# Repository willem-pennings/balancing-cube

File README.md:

## Balancing cube

This repository contains all design, documentation, configuration and other files related to the balancing cube that I have designed and built.
* Mechanical parts are designed in [Fusion 360](https://www.autodesk.com/products/fusion-360/personal).
* Circuit boards are designed in [KiCad 7](https://www.kicad.org/download/windows/).
* Code has been written using [Arduino IDE](https://docs.arduino.cc/software/ide-v2/tutorials/getting-started/ide-v2-downloading-and-installing/).
* Motor drivers are commissioned and tuned using [Escon Studio](https://www.maxongroup.nl/maxon/view/content/ESCON-Detailsite?isoCode=nl).
* Motors and motor controllers are available from [Maxon](https://www.maxongroup.com/maxon/view/content/index).
* Circuit boards and custom mechanical parts can be ordered from [PCBWay](https://www.pcbway.com/rapid-prototyping/), for example.

A YouTube video demonstrating the balancing cube is available [here](https://youtu.be/zGclFqkZBsk).

### Want to build one? Read this!

This repository should contain everything you need to order and/or build parts for this cube. Take into account the following:

* I replaced four of the eight 16AWG wires in each cable assembly by 22AWG wires since only four wires carry large currents. The others carry +5V and hall sensor signals. This reduces weight and makes the cables easier to handle, as well as reducing strain on the mating connectors. The motor connection is rather fragile and might break if stressed too much.
* The ESP32 board does not go into flashing mode automatically. I fixed this by adding a 10 uF capacitor between the enable and reset pin, as described [here](https://randomnerdtutorials.com/solved-failed-to-connect-to-esp32-timed-out-waiting-for-packet-header/).
* In my blog post, I describe some errors in the design of the motherboard. These have been resolved in the files that are available in this repository.
* For your own safety, I highly recommend taking precautions to reduce the risk of trapping fingers between the spinning flywheels. One option is to attach very thin (spring steel) discs to each wheel, which may be (laser)cut from larger sheets that are readily available. I do not have designs available for such safety devices yet.

### More information

More information about this project and my other projects is available on my [website](https://willempennings.nl/balancing-cube/).

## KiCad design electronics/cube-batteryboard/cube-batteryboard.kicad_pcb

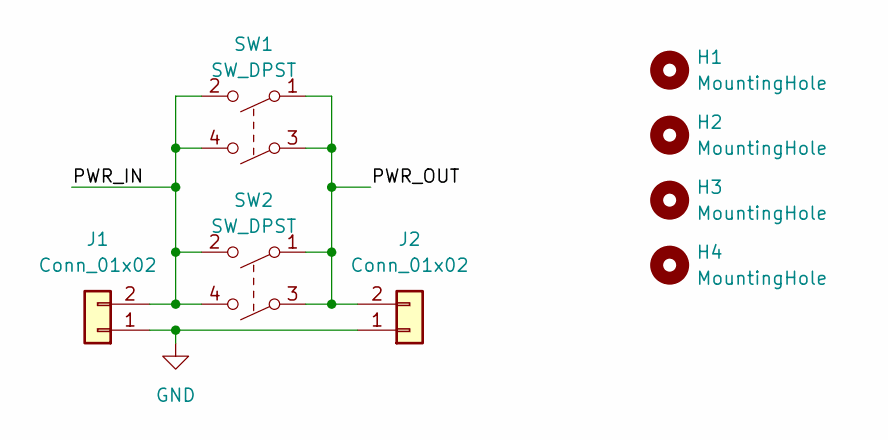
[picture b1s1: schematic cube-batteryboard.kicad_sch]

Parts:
H1, H2, H3, H4: MountingHole; MountingHole_3.2mm_M3_DIN965_Pad
J1: Conn_01x02; AMASS_XT60-M_1x02_P7.20mm_Vertical
J2: Conn_01x02; AMASS_XT60-F_1x02_P7.20mm_Vertical
SW1, SW2: SW_DPST; L201011MS02Q

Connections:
/PWR_IN: J1.2, SW1.2, SW1.4, SW2.2, SW2.4
/PWR_OUT: J2.2, SW1.1, SW1.3, SW2.1, SW2.3
GND: J1.1, J2.1

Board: 2 copper layers, 13 parts (9 on the bottom side), 3 nets, no tracks yet.

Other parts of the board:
kibuzzard-65634FCA: G***; kibuzzard-65634FCA
kibuzzard-656351C1: G***; kibuzzard-656351C1
kibuzzard-656351D2: G***; kibuzzard-656351D2
kibuzzard-656351E7: G***; kibuzzard-656351E7
kibuzzard-65635119: G***; kibuzzard-65635119

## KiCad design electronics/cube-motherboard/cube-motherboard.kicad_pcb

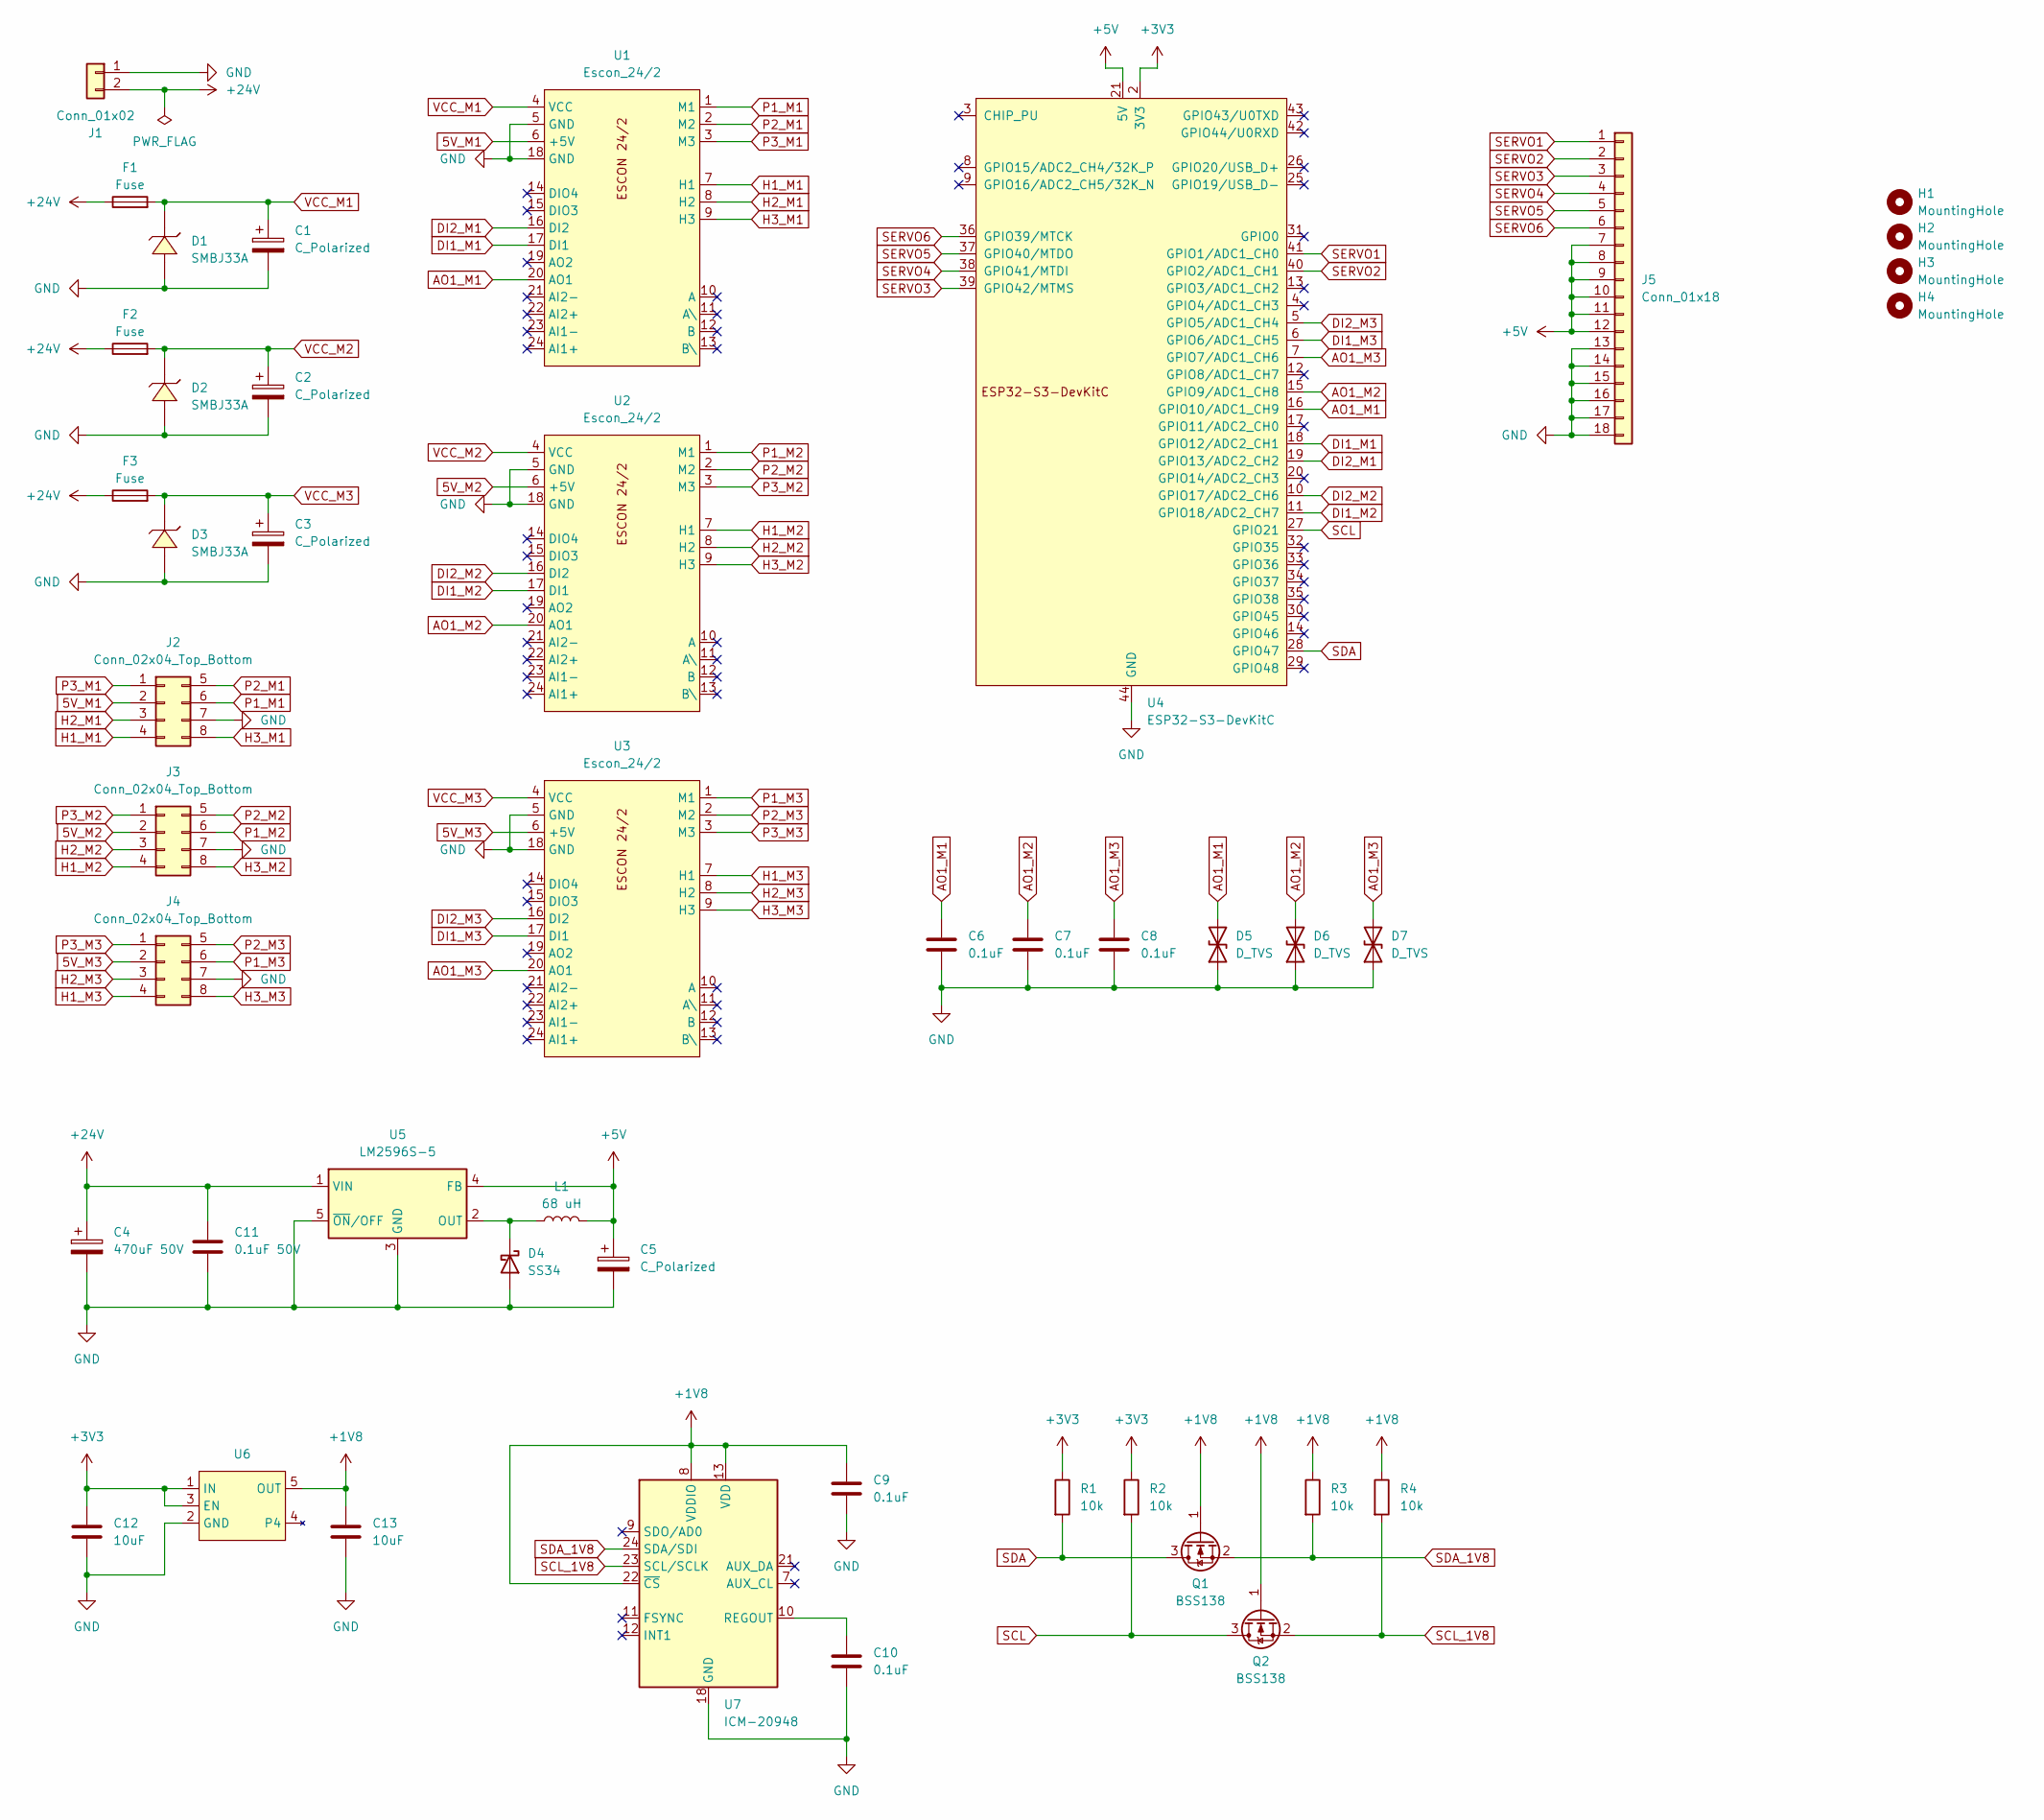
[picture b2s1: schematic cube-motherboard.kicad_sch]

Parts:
C1, C2, C3: C_Polarized; CP_Radial_D12.5mm_P5.00mm
C4: 470uF 50V; CP_Radial_D18.0mm_P7.50mm
C5: C_Polarized; CP_Radial_D10.0mm_P5.00mm
C6, C7, C8, C9, C10: 0.1uF; C_0603_1608Metric
C11: 0.1uF 50V; C_0603_1608Metric
C12, C13: 10uF; C_0603_1608Metric
D1, D2, D3: SMBJ33A; SMB_L4.4-W3.6-LS5.4-RD
D4: SS34; D_SOD-123F
D5, D6, D7: D_TVS; D_0402_1005Metric
F1, F2, F3: Fuse; Littelfuse 0157004.DR
H1, H2, H3, H4: MountingHole; MountingHole_3.2mm_M3_DIN965_Pad
J1: Conn_01x02; AMASS_XT60-F_1x02_P7.20mm_Vertical
J2, J3, J4: Conn_02x04_Top_Bottom; Molex_Mini-Fit_Jr_5566-08A_2x04_P4.20mm_Vertical
J5: Conn_01x18; PinHeader_03x06
L1: 68 uH; Bourns SRP1050WA-680M
Q1, Q2: BSS138; SOT-23
R1, R2, R3, R4: 10k; R_0603_1608Metric
U1, U2, U3: Escon_24/2; Escon_24
U4: ESP32-S3-DevKitC
U5: LM2596S-5; TO-263-5_TabPin3
U6: SOT-23-5
U7: ICM-20948; InvenSense_QFN-24_3x3mm_P0.4mm

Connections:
5V_M1: J2.2, U1.6 (+5V)
5V_M2: J3.2, U2.6 (+5V)
5V_M3: J4.2, U3.6 (+5V)
+1V8: C9.1, C13.1, Q1.1 (G), Q2.1 (G), R3.1, R4.1, U6.5 (OUT), U7.8 (VDDIO), U7.13 (VDD), U7.22 (~CS)
+3V3: C12.1, R1.1, R2.1, U4.1 (3V3), U4.2 (3V3), U6.1 (IN), U6.3 (EN)
+5V: C5.1, J5.7, J5.8, J5.9, J5.10, J5.11, J5.12, L1.2, U4.21 (5V), U5.4 (FB)
+24V: C4.1, C11.1, F1.1, F2.1, F3.1, J1.2, U5.1 (VIN)
AO1_M1: C6.1, D5.2 (A2), U1.20 (AO1), U4.16 (GPIO10/ADC1_CH9)
AO1_M2: C7.1, D6.2 (A2), U2.20 (AO1), U4.15 (GPIO9/ADC1_CH8)
AO1_M3: C8.1, D7.2 (A2), U3.20 (AO1), U4.7 (GPIO7/ADC1_CH6)
DI1_M1: U1.17 (DI1), U4.18 (GPIO12/ADC2_CH1)
DI1_M2: U2.17 (DI1), U4.11 (GPIO18/ADC2_CH7)
DI1_M3: U3.17 (DI1), U4.6 (GPIO6/ADC1_CH5)
DI2_M1: U1.16 (DI2), U4.19 (GPIO13/ADC2_CH2)
DI2_M2: U2.16 (DI2), U4.10 (GPIO17/ADC2_CH6)
DI2_M3: U3.16 (DI2), U4.5 (GPIO5/ADC1_CH4)
GND: C1.2, C2.2, C3.2, C4.2, C5.2, C6.2, C7.2, C8.2, C9.2, C10.2, C11.2, C12.2, C13.2, D1.2 (A), D2.2 (A), D3.2 (A), D4.2 (A), D5.1 (A1), D6.1 (A1), D7.1 (A1), J1.1, J2.7, J3.7, J4.7, J5.13, J5.14, J5.15, J5.16, J5.17, J5.18, U1.5 (GND), U1.18 (GND), U2.5 (GND), U2.18 (GND), U3.5 (GND), U3.18 (GND), U4.22 (GND), U4.23 (GND), U4.24 (GND), U4.44 (GND), U5.3 (GND), U5.5 (~ON/OFF), U6.2 (GND), U7.18 (GND), U7.20 (GND)
H1_M1: J2.4, U1.7 (H1)
H1_M2: J3.4, U2.7 (H1)
H1_M3: J4.4, U3.7 (H1)
H2_M1: J2.3, U1.8 (H2)
H2_M2: J3.3, U2.8 (H2)
H2_M3: J4.3, U3.8 (H2)
H3_M1: J2.8, U1.9 (H3)
H3_M2: J3.8, U2.9 (H3)
H3_M3: J4.8, U3.9 (H3)
unnamed: D4.1 (K), L1.1, U5.2 (OUT)
unnamed: C10.1, U7.10 (REGOUT)
P1_M1: J2.6, U1.1 (M1)
P1_M2: J3.6, U2.1 (M1)
P1_M3: J4.6, U3.1 (M1)
P2_M1: J2.5, U1.2 (M2)
P2_M2: J3.5, U2.2 (M2)
P2_M3: J4.5, U3.2 (M2)
P3_M1: J2.1, U1.3 (M3)
P3_M2: J3.1, U2.3 (M3)
P3_M3: J4.1, U3.3 (M3)
SCL: Q2.3 (D), R2.2, U4.27 (GPIO21)
SCL_1V8: Q2.2 (S), R4.2, U7.23 (SCL/SCLK)
SDA: Q1.3 (D), R1.2, U4.28 (GPIO47)
SDA_1V8: Q1.2 (S), R3.2, U7.24 (SDA/SDI)
SERVO1: J5.1, U4.41 (GPIO1/ADC1_CH0)
SERVO2: J5.2, U4.40 (GPIO2/ADC1_CH1)
SERVO3: J5.3, U4.39 (GPIO42/MTMS)
SERVO4: J5.4, U4.38 (GPIO41/MTDI)
SERVO5: J5.5, U4.37 (GPIO40/MTDO)
SERVO6: J5.6, U4.36 (GPIO39/MTCK)
VCC_M1: C1.1, D1.1 (C), F1.2, U1.4 (VCC)
VCC_M2: C2.1, D2.1 (C), F2.2, U2.4 (VCC)
VCC_M3: C3.1, D3.1 (C), F3.2, U3.4 (VCC)

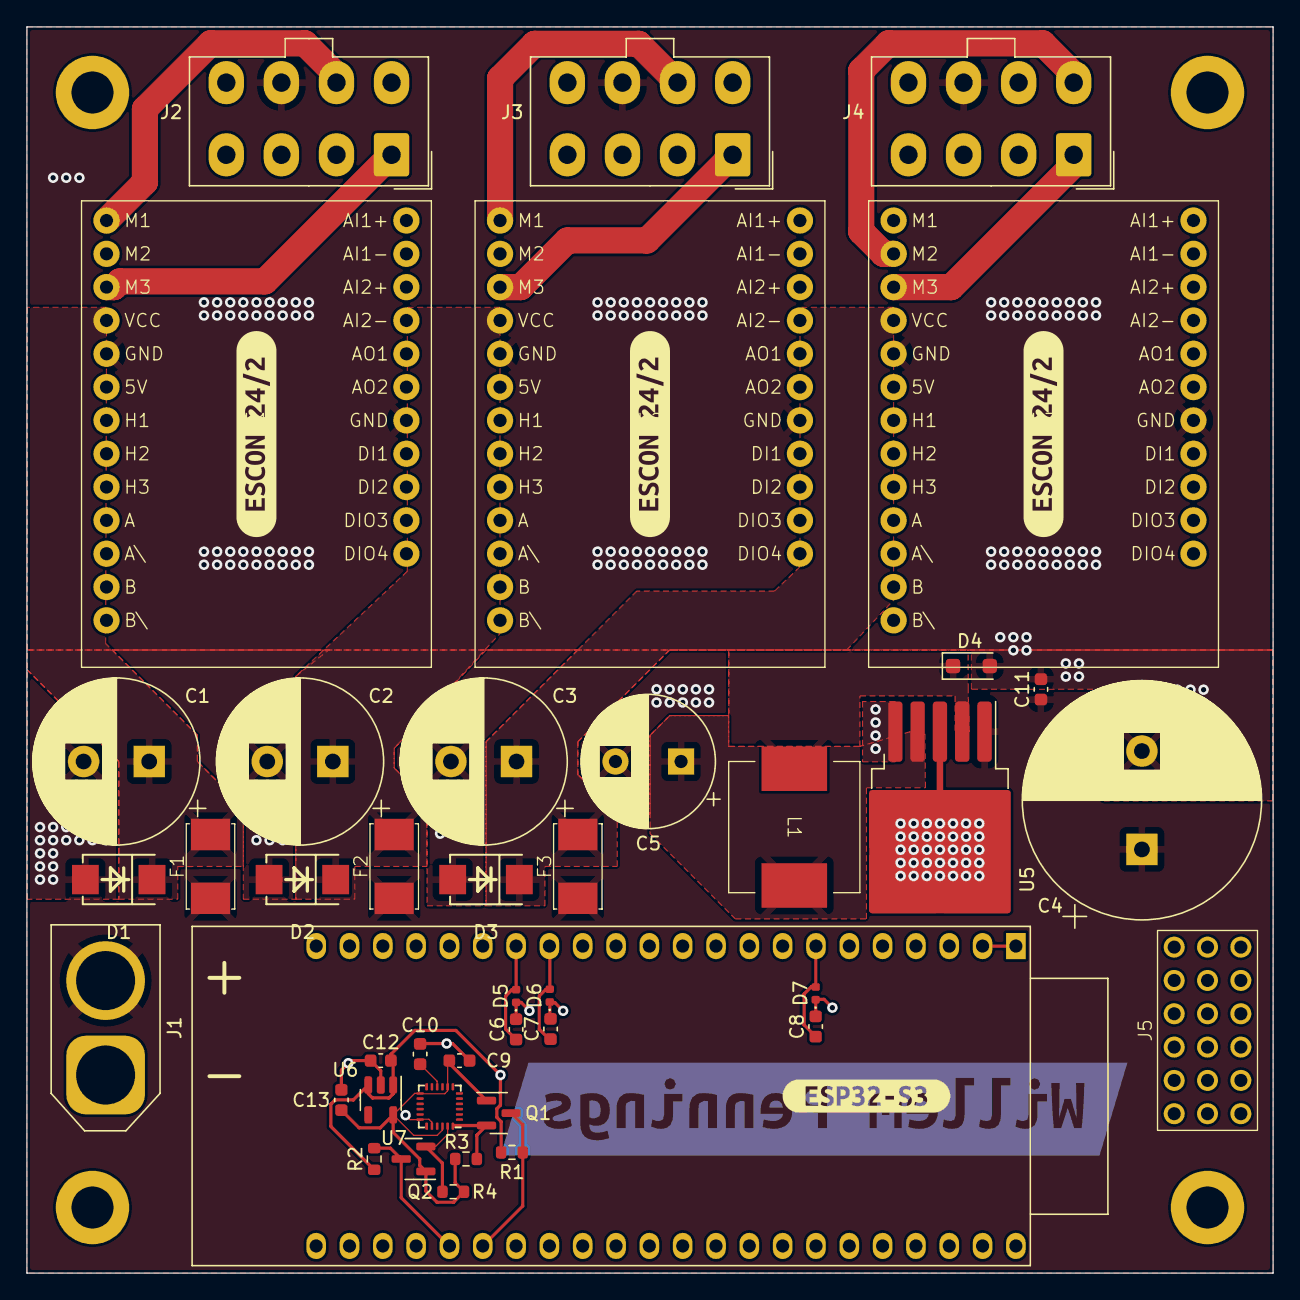
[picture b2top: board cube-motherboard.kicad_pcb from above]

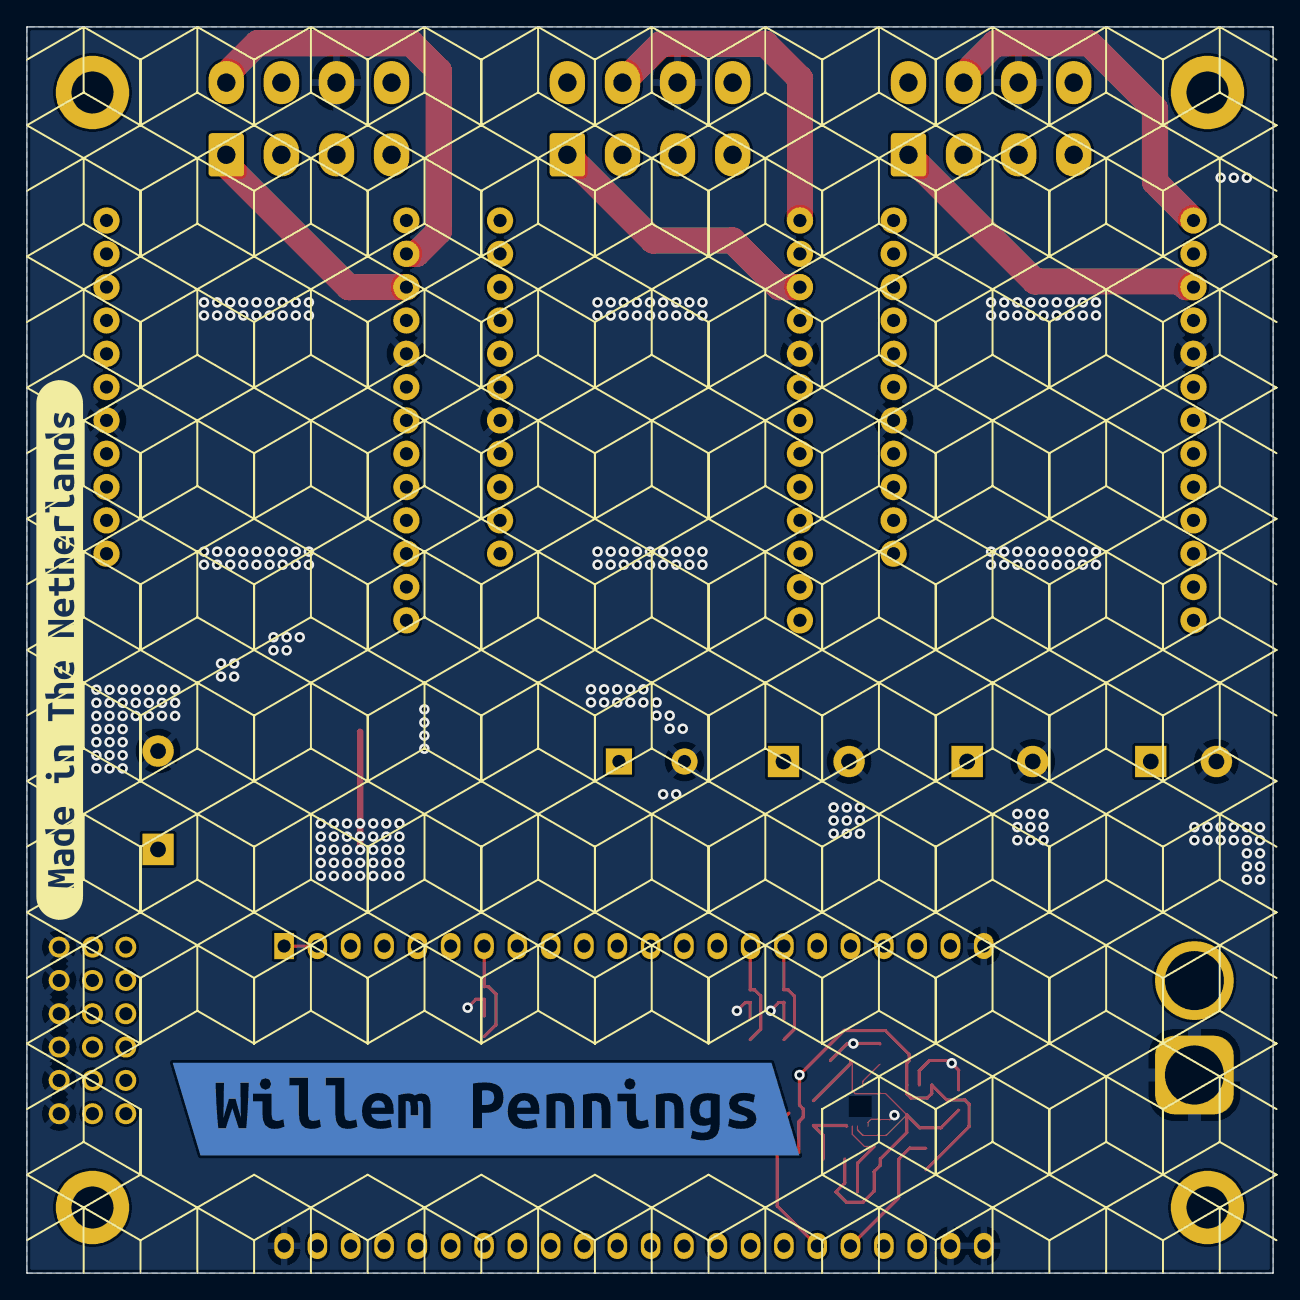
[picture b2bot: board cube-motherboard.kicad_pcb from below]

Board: 4 copper layers, 95.0 x 95.0 mm, 52 parts (2 on the bottom side), 50 nets.

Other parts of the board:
kibuzzard-65625AD1: G***; kibuzzard-65625AD1
kibuzzard-65625B38: G***; kibuzzard-65625B38
kibuzzard-65625B53, kibuzzard-65625B53#2, kibuzzard-65625B53#3: G***; kibuzzard-65625B53
kibuzzard-656267AE: G***; kibuzzard-656267AE

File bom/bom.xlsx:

Quantity | Name | Designators | Part number | Supplier
3 | Aluminium Electrolytic Capacitors - Radial Leaded 120uF 63 Volts 20% | C1, C2, C3 | 647-UPM1J121MHD6TO | Mouser
1 | Aluminium Electrolytic Capacitors - Radial Leaded 50volts 470uF 18x15 20% 7.5LS | C4 | 647-UPJ1H471MHD6 | Mouser
1 | Aluminium Electrolytic Capacitors - Radial Leaded 25volts 220uF 10x12.5 '20% 5LS | C5 | 647-UPJ1E221MPD6 | Mouser
6 | Multilayer Ceramic Capacitors MLCC - SMD/SMT 50V 0.1uF X7R 0603 10% Flex AEC-Q2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 | C6, C7, C8, C9, C10, C11 | 80-C0603X104K5R3316 | Mouser
2 | Multilayer Ceramic Capacitors MLCC - SMD/SMT 10V 10uF X5R 0603 20% | C12, C13 | 80-C0603C106M8PACTU | Mouser
3 | ESD Suppressors / TVS Diodes 33V 1000W UniDir TransZorb 5% Tol | D1, D2, D3 | 78-SMBJ33A | Mouser
1 | Schottky Diodes & Rectifiers 40V 3A SCHOTTKY RECTIF | D4 | 863-NRVBSS34FA | Mouser
3 | ESD Suppressors / TVS Diodes 3.3V Bidirectional | D5, D6, D7 | 652-CDDFN2-T3.3B | Mouser
3 | Surface Mount Fuses 260C 4A SMF NANO CLIP VFA | F1, F2, F3 | 576-0157004.DR | Mouser
4 | XT60 connector female |  | 474-PRT-10474 | Mouser
4 | XT60 connector male | J1 | 474-PRT-10474 | Mouser
3 | Headers & Wire Housings 8 CKT VERT HEADER | J2, J3, J4 | 538-39-28-1083 | Mouser
3 | Rectangular Cable Assemblies MINIFIT JR DR R-R 8CKT 150MM Sn |  | 538-215325-1081 | Mouser
1 | Headers & Wire Housings Classic PCB Header Strips, 0.100" pitch | J5 | 200-TSW10607LT | Mouser
1 | Power Inductors - SMD Ind,11x10x5.1mm,68uH+/-20%,3.5A,shd | L1 | 652-SRP1050WA-680M | Mouser
2 | MOSFET 50V, 0.26A, Single N-Channel Power MOSFET | Q1, Q2 | 821-BSS138 | Mouser
4 | Thick Film Resistors - SMD 10K OHM 5% | R1, R2, R3, R4 | 71-RCA060310K0JNEA | Mouser
1 | WiFi Development Tools - 802.11 ESP32-S3 Gen-Purpose Dev Bd, ESP32-S3-WROOM-1 | U4 | 356-EP32S3DVKTC1N8R8 | Mouser
1 | Switching Voltage Regulators 150 KHZ 3A STEP-DOWN VLTG REG | U5 | 926-LM2596SX-5.0NOPB | Mouser
1 | LDO Voltage Regulators High Vin, Low Iq Regulator | U6 | 998-MIC5225-1.8YM5TR | Mouser
1 | IMUs - Inertial Measurement Units World's Lowest Power 9-Axis MEMS MotionTracki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 | U7 | 410-ICM-20948 | Mouser
7 | Headers & Wire Housings |  | 801-87-011-10-005101 | Mouser
3 | Headers & Wire Housings |  | 801-87-013-10-005101 | Mouser
2 | Slide Switches Slide DPST | SW1, SW2 | 611-L201011MS02Q | Mouser
3 | EC 45 flat ∅42.8 mm, brushless, 60 W, with Hall sensors | Open rotor |  | 591477 | Maxon
3 | ESCON Module 24/2, 4-Q servo controller for DC/EC motors, 2/6 A, 10-24 VDC |  | 466023 | Maxon
3 | Machined part: motor frame (aluminium 6061)
3 | Machined part: regular frame (aluminium 6061)
3 | Machined part: bridge (stainless steel 304)
3 | Machined part: hub (stainless steel 304)
3 | Machined part: wheel (stainless steel 304)
4 | Machined part: Cornerstone A/CW (stainless steel 304)
4 | Machined part: Cornerstone B/CCW (stainless steel 304)
1 | Tattu Funfly Series 1300mAh 22.2V 100C 6S1P LiPo
1 | Custom PCB: cube-motherboard (4-layer ENIG)
1 | Custom PCB: cube-batteryboard (2-layer HASL)
9 | Machine screw M3x6 countersunk (motor - bridge)
8 | Machine screw M3x10 countersunk (frame - batteryboard, frame - motherboard)
8 | Nut M3
8 | Nylon spacer black ID 3.2 mm OD 7 mm
9 | Set screw hex M3x4 (hub - motor)
9 | Machine screw M2x6 countersunk (wheel - hub)
36 | Machine screw M3x8 countersunk (cornerstone - frame, frame - bridge)
3 | Radial ball bearing, 4 mm x 9 mm x 4 mm (bore diameter x outer diameter x width) |  | 638-4-ZZ-SKF

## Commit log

2024-02-10 Create LICENSE
2024-02-10 Publish files
2024-02-10 Add photo of cube
2024-02-21 Add bearings to BOM
2024-05-29 Fix unconnected GND circuit for J2 (pin 1)
2024-06-08 Add gitignore
2024-06-20 Fix incorrect controller gains
2024-06-20 Organize esp32 <-> escon wiring
    Remapped AO1 of M3 to an ADC1 pin.
    Removed all three unused AO2 DI3 wirings and relevant diodes and capacitors
    Corrected pins.h (Old version was not matching with old schematic btw)
    Updated Bom accordingly
2024-06-20 Fix symbol, footprint and orientation of D1,D2 and D3 diodes
    Add missing 3D models for L1 & F1,F2,F3
2024-06-20 fix labels for on off switch
2024-06-21 Remove the requirement to remap the pins of the molex cables by reorganizing pin order
